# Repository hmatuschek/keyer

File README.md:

# Electronic touch CW keyer
This tiny circuit and its firmware implements a simple electronic CW keyer using capacitive touch-paddles. Hence it has absolutely no moving parts which eases the build of the mechanical part of the keyer a lot. 

The central logic of the keyer is implemented in software using a ATTiny 45 MCU. It implements a simple (mode A) electronic CW key. The capacitive touch interface is easy too. It basically measures the capacity of the metal paddles which changes as they get touched with the hand. In fact, the hardware measures the time needed to charge the paddles though a large resistor. This time increases significantly if the paddle is touched. 

The circuit provides a open-collector output to switch even simple transmitters which expect a straight key. Additionally an LED and a side-tone generator are present for practicing. The speed of the keyer can be set using a potentiometer in a range from 10WPM to 42WPM. Please note that the speed gets updated only while the key is idle.

## License
Both, the hard and software are licensed under the terms of the GNU Public License (GPL).

Copyright (C) 2015  Hannes Matuschek <hmatuschek at gmail dot com>

This program is free software; you can redistribute it and/or modify it under the terms of the GNU General Public License as published by the Free Software Foundation; either version 2 of the License, or (at your option) any later version.

This program is distributed in the hope that it will be useful, but WITHOUT ANY WARRANTY; without even the implied warranty of MERCHANTABILITY or FITNESS FOR A PARTICULAR PURPOSE.  See the GNU General Public License for more details.

You should have received a copy of the GNU General Public License along with this program; if not, write to the Free Software Foundation, Inc., 51 Franklin Street, Fifth Floor, Boston, MA 02110-1301 USA.

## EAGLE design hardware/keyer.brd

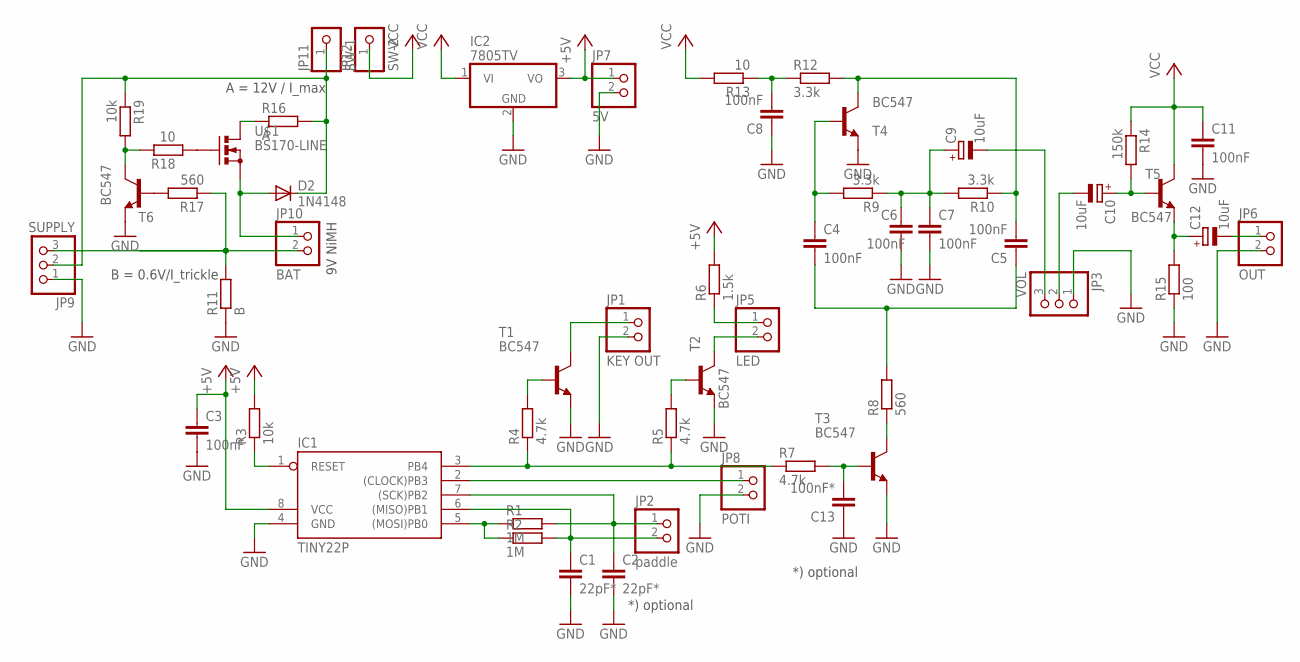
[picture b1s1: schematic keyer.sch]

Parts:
C1, C2: 22pF*; C050-025X075
C3: 100nF; C075-032X103
C4, C5, C6, C7, C8, C11: 100nF; C025-025X050
C9, C10, C12: 10uF; E2,5-6
C13: 100nF*; C025-025X050
D2: 1N4148; D-2.5
IC1: TINY22P; DIL08
IC2: 7805TV; TO220V
JP1: KEY OUT; 1X02
JP2: paddle; 1X02
JP3: VOL; 1X03
JP5: LED; 1X02
JP6: OUT; 1X02
JP7: 5V; 1X02
JP8: POTI; 1X02
JP9: SUPPLY; 1X03
JP10: BAT; 1X02
JP11: SW-1; 1X01
JP12: SW-2; 1X01
R1: 1M; 0204/5
R2: 1M; 0204V
R3: 10k; 0204/5
R4, R5, R7: 4.7k; 0204/5
R6: 1.5k; 0204/5
R8: 560; 0204V
R9, R12: 3.3k; 0204/5
R10: 3.3k; 0204/7
R11: B; 0204/5
R13: 10; 0204V
R14: 150k; 0204V
R15: 100; 0204/7
R16: A; 0204V
R17: 560; 0204/5
R18: 10; 0204/5
R19: 10k; 0204V
T1, T2, T3, T4, T5, T6: BC547; TO92-CBE
U$1: BS170-LINE; TO92-LINE

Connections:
+5V: C3.1, IC1.8 (VCC), IC2.3 (VO), JP7.1, R3.2, R6.2
GND: C1.2, C2.2, C3.2, C6.2, C7.2, C8.1, C11.2, C13.1, IC1.4 (GND), IC2.2 (GND), JP1.2, JP3.1, JP6.2, JP7.2, JP8.2, JP9.1, R11.1, R15.1, T1.E, T2.E, T3.E, T4.E, T6.E
unnamed: IC1.5 ((MOSI)PB0), R1.1, R2.1
unnamed: C2.1, IC1.7 ((SCK)PB2), JP2.1, R1.2
unnamed: C1.1, IC1.6 ((MISO)PB1), JP2.2, R2.2
unnamed: IC1.1 (RESET), R3.1
unnamed: IC1.2 ((CLOCK)PB3), JP8.1
unnamed: R4.2, T1.B
unnamed: JP1.1, T1.C
unnamed: IC1.3 (PB4), R4.1, R5.1, R7.1
unnamed: R8.1, T3.C
unnamed: R5.2, T2.B
unnamed: JP5.2, T2.C
unnamed: JP5.1, R6.1
unnamed: C4.1, R9.2, T4.B
unnamed: C13.2, R7.2, T3.B
unnamed: C5.2, R10.1, R12.2, T4.C
unnamed: JP9.3, JP10.2, R11.2, R17.1
unnamed: C6.1, C7.1, C9.+, R9.1, R10.2
unnamed: C4.2, C5.1, R8.2
unnamed: C8.2, R12.1, R13.1
unnamed: C9.-, JP3.3
unnamed: C10.-, JP3.2
unnamed: C10.+, R14.2, T5.B
unnamed: C12.+, R15.2, T5.E
unnamed: C12.-, JP6.1
unnamed: R17.2, T6.B
unnamed: D2.A, JP10.1, U$1.1 (S)
unnamed: R16.1, U$1.3 (D)
unnamed: R18.1, U$1.2 (G)
unnamed: R18.2, R19.2, T6.C
unnamed: D2.C, JP9.2, JP11.1, R16.2, R19.1
VCC: C11.1, IC2.1 (VI), JP12.1, R13.2, R14.1, T5.C

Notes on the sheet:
9V NiMH
A = 12V / I_max
B = 0.6V/I_trickle
*) optional

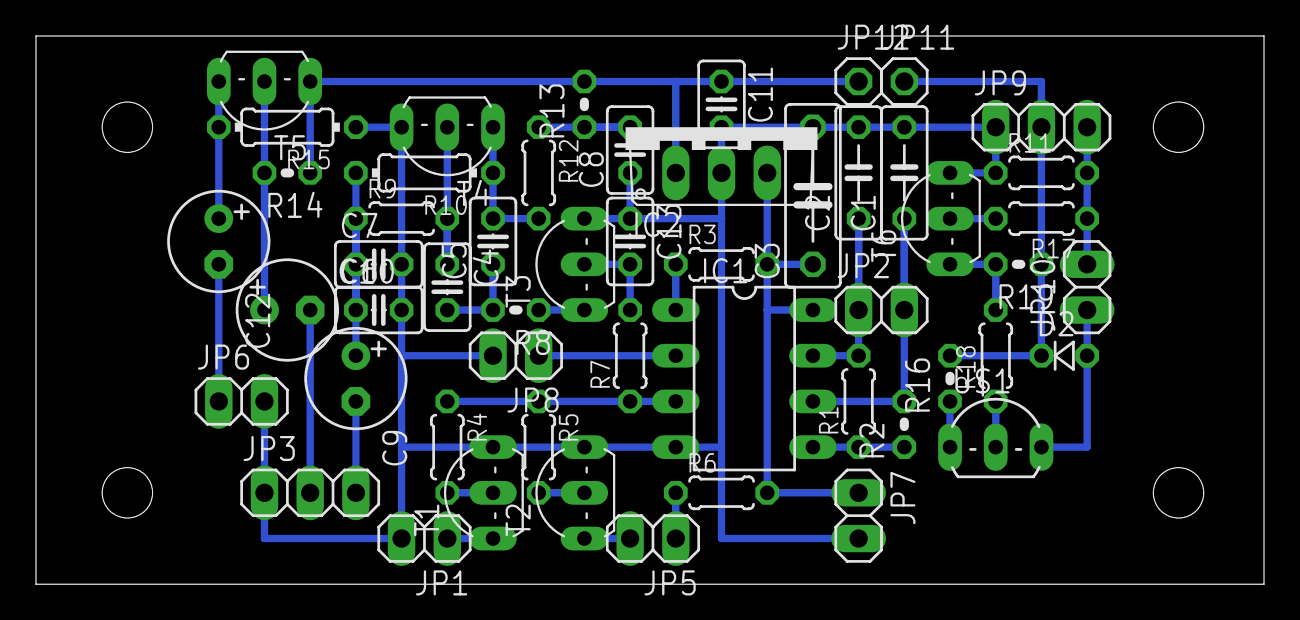
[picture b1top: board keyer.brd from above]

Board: 2 copper layers, 68.2 x 30.5 mm, 53 parts (0 on the bottom side), 33 nets.

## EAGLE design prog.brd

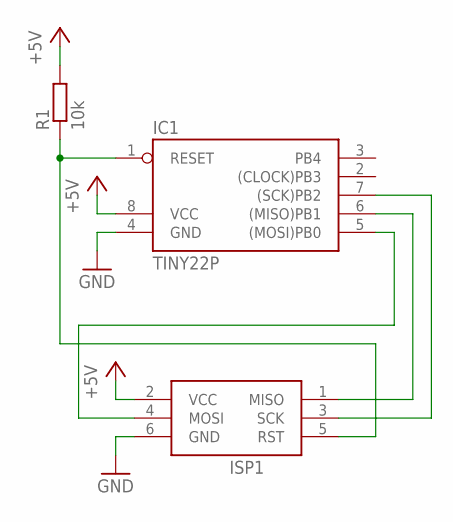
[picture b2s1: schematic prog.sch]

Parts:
IC1: TINY22P; DIL08
ISP1: AVRISP-6; AVRISP
R1: 10k; 0204/7

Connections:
+5V: IC1.8 (VCC), ISP1.2 (VCC), R1.2
GND: IC1.4 (GND), ISP1.6 (GND)
unnamed: IC1.1 (RESET), ISP1.5 (RST), R1.1
unnamed: IC1.5 ((MOSI)PB0), ISP1.4 (MOSI)
unnamed: IC1.6 ((MISO)PB1), ISP1.1 (MISO)
unnamed: IC1.7 ((SCK)PB2), ISP1.3 (SCK)

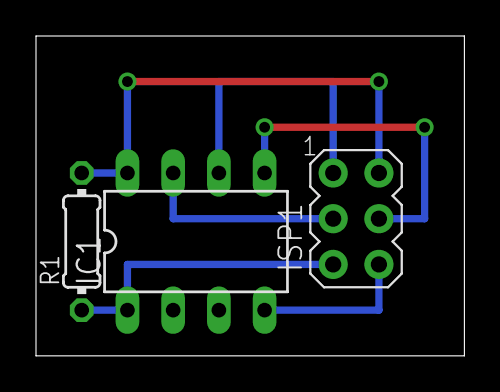
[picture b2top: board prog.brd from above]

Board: 2 copper layers, 23.8 x 17.8 mm, 3 parts (0 on the bottom side), 6 nets.

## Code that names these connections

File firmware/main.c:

/* Firmware for the CW touch key (paddle).
 *
 * (c) 2015, Hannes Matuschek <hmatuschek at gmail dot com>
 *
 * This firmware implements an electronic key using two simple metal paddles
 * (connected to PB1 & PB2) that are triggered by touching them. Touching a paddle causes the
 * capacity of the paddle to increase. This can be detected by measureing the time needed to charge
 * the paddle through a huge resistor (about 1MOhm). Touching the left paddle will generate a series
 * of dots (dit) while touching the right paddle will generate a series of dahses (dah). Touching
 * both paddles at the same time, a series of dot and dash alternations are generated. If the left
 * paddle was touched first, the series starts with a dash. If the right paddle was
 * touched first, the series starts with a dot. This is equivalent to the behavior of an
 * iambic CW key (mode A).
 *
 * The speed (between 10 and 43 WPM) can be chosen by a potentiometer connected to PB3 (ADC3). The
 * output is connected to PB4. This pin controls an open-collector output to controll the
 * transmitter, an LED and a 600Hz side-tone generator.
 */

#include <avr/io.h>
#include <avr/interrupt.h>
#include <util/delay.h>
#include <avr/cpufunc.h>
#include <avr/pgmspace.h>

/// Keep the delay short
#define MAX_DELAY (F_CPU/1000UL)
/// Helper macro to return the maximum of two values
#define max(a,b) (a<b ? b : a)


// LUT of 32 dit-lengths values (in ms),
// (approx) linear in WPM, from 10 to 42 WPM.
static const uint16_t dit_len_lut[] = {
  120, 109, 100,  92,  86,  80,  75,  70,
   67,  63,  60,  57,  54,  52,  50,  48,
   46,  44,  43,  41,  40,  39,  37,  36,
   35,  34,  33,  32,  31,  30,  29,  28};


/// Initializes the touch interface
void init_touch() {
  // set PB0 as output
  DDRB  |= (1 << DDB0);
  // set PB0 to 0
  PORTB &= ~(1 << DDB0);
  // set PB1 & PB2 as output (low Z, for now)
  DDRB  |= ((1 << DDB1) | (1 << DDB2));
  // set 0 (GND), keeps paddles discharged
  PORTB &= ~((1 << DDB1) | (1 << DDB2));
}

/// Read touch paddles, returns 0b00 if no paddle is touched,
/// 0b01 if only the left is touched, 0b10 if only the right is
/// touched and 0b11 if both are touched.
uint8_t read_touch(uint32_t thres) {
  // config sense pins as input (high impedance)
  DDRB  &= ~((1<<DDB1) | (1<<DDB2));
  // start charging, set PB0 -> 1
  PORTB |= (1<<DDB0);
  // delay
  for (uint32_t i=0; i<thres; i++) { _NOP(); }
  // check values (if the pin is still 0, the paddle is touched).
  uint8_t value = ((PINB>>1) & 0x03) ^ 0x03;
  // discharge paddles...
  PORTB &= ~(1<<DDB0);  // set PB0 -> 0
  // ... set sense pins as output (low impedance)
  DDRB  |= ((1<<DDB1) | (1<<DDB2));
  // ... set sense pin to 0 (GND)
  PORTB &= ~( (1<<DDB1) || (1<<DDB2) );
  // wait for a short time to discharge completely
  _delay_us(10);
  // done.
  return value;
}

/// Calibrate the touch interface
uint32_t calibrate_touch() {
  uint32_t thres = 1;
  // Increment threshold until touch detects no value
  while (read_touch(thres) && (thres<MAX_DELAY)) {
    thres++;
  }
  // Increase threshold for reliable detection
  // (this decreses the sensitivity for the sake
  // of reduced false-positives). The factor depends
  // on the hardware and may you need to experiment with
  // this value.
  return 2*thres;
}


/// Configures the timer interrupt to be triggered every 1ms.
void init_timer() {
  // Set Timer on Compare Match (CTC) mode
  TCCR0A = 0x02;
  // clock source CLK/16
  TCCR0B = 0x03;
  // -> 1ms
  OCR0A  = 125-1;
  // enable interrupt (OC 0A)
  TIMSK  = (1<<OCIE0A);
}


/// Configures the output.
void init_key() {
  // set PB4 as output
  DDRB  |= (1 << DDB4);
  PORTB &= ~(1 << DDB4);
}

/// Sets the output.
void key(uint8_t on) {
  if (on) { PORTB |= (1<<DDB4); }
  else { PORTB &= ~(1<<DDB4); }
}

/// Toggles the output.
void toggle_key() {
  PORTB ^= (1<<DDB4);
}


/// Initializes the ADC.
void init_adc() {
  // Set as input (high Z)
  DDRB  &= ~(1 << DDB3);
  // Disable digital input buffer of PB3
  DIDR0 |= (1 << ADC3D);
  // Config prescaler (no iterrupt, auto trigger, ADC still disabled)
  ADCSRA = (0 << ADEN) | (0 << ADSC) | (0 << ADATE) | (0 << ADIF) | (0 << ADIE) |
      (1<<ADPS2) | (1<<ADPS1) | (1<<ADPS0);
  // Vcc reference, ADC3 input
  ADMUX = (0<<REFS2) | (0<<REFS1) | (0<<REFS0) | (0<<ADLAR) |
      (0<<MUX3) | (0<<MUX2) | (1<<MUX1) | (1<<MUX0);
  // enable ADC
  ADCSRA |= (1<<ADEN);
}

/// Starts a new conversion.
void start_adc() {
  ADCSRA |= (1<<ADSC);
}

/// Returns true if the ADC is ready.
uint8_t adc_available() {
  return (0 == (ADCSRA & (1<<ADSC)));
}

/// Returns the ADC value as a 5-bit (0,...,31) value.
uint8_t adc_value() {
  return (ADCW>>5);
}

/// Returns the dit length in ms as defined by the ADC value.
uint16_t get_dit_len() {
  // Simply return the corresponding LUT value
  //return pgm_read_word_near(&dit_len_lut[adc_value() % 32]);
  return dit_len_lut[adc_value() % 32];
}


/** Possible states of the state machine. */
typedef enum {
  IDLE,         ///< Idle, wait for keys.
  SEND_DIT,     ///< Send a dit.
  SEND_DAH      ///< Send a dah.
} State;

/// The current state.
volatile State state = IDLE;
/// The last state.
volatile State last_state = IDLE;
/// The current dit length in ms.
/// Gets updated on startup.
volatile uint16_t dit_len = 60;
// Precomputed multiples of ditlen
volatile uint16_t dit_2len = 2*60;
volatile uint16_t dit_3len = 3*60;
volatile uint16_t dit_4len = 4*60;


int main(void)
{
  // Init timer interrupt
  init_timer();
  // Init touch interface
  init_touch();
  // Init output
  init_key();
  // Init ADC
  init_adc();

  // Calibrate the touch interface,
  // take the maximum threshold from 100 trials
  uint32_t thres = 0;
  for (uint8_t i=0; i<100; i++) {
    thres = max(thres, calibrate_touch());
  }

  // on calibration error
  // (delay threshold to large, sould not happen)
  while (MAX_DELAY == thres) {
    // -> blink trap
    toggle_key();
    _delay_ms(200);
  }

  // Measure speed setting...
  start_adc();
  // ... wait for the ADC to finish
  while (! adc_available()) { }
  // ... compute dit lenght
  dit_len = get_dit_len();
  // ... precompute some multiples of dit len
  dit_2len = 2*dit_len; dit_3len = 3*dit_len; dit_4len = 4*dit_len;

  // enable interrupts globally
  sei();

  // Go.
  state = IDLE;
  last_state = IDLE;

  // Poll paddles.
  while(1)
  {
    // If waiting for the next symbol...
    if (IDLE == state) {
      // ... dispatch by paddle state
      // (left -> dit, right -> dah, both -> alternate dit & dah)
      switch (read_touch(thres)) {
        // On left paddle
        case 0x01:
          last_state = IDLE;
          state = SEND_DIT;
          break;

        // On right paddle
        case 0x02:
          last_state = IDLE;
          state = SEND_DAH;
          break;

        // On both paddles alternate dit & dah
        case 0x03:
          if (SEND_DIT == last_state) {
            // If last state was a dit -> send dah
            last_state = SEND_DIT;
            state = SEND_DAH;
          } else {
            // If last state was a dah -> send dit
            last_state = state;
            state = SEND_DIT;
          }
          break;

        // Otherwise stay in idle
        default:
          break;
      }

      // If still in idle -> check speed dial and update dit length
      if ((IDLE == state) && adc_available()) {
        // If ADC is ready, update dit len
        dit_len = get_dit_len();
        // Precompute multiples of dit len
        dit_2len = 2*dit_len; dit_3len = 3*dit_len; dit_4len = 4*dit_len;
        // and restart measurement
        start_adc();
      }
    }
  }
}


ISR (TIMER0_COMPA_vect)
{
  static uint16_t count = 0;

  if (SEND_DIT == state) {
    // Send a dit (10, with additional pause)
    if (0 == count) {
      key(1); count++;
    } else if (dit_len == count) {
      key(0); count++;
    } else if (dit_2len == count) {
      last_state = SEND_DIT;
      state = IDLE;
      count = 0;
    } else {
      count++;
    }
  } else if (SEND_DAH == state) {
    // Send a dah (1110, with additional pause)
    if (0 == count) {
      key(1); count++;
    } else if (dit_3len == count) {
      key(0); count++;
    } else if (dit_4len == count) {
      last_state = SEND_DAH;
      state = IDLE;
      count = 0;
    } else {
      count++;
    }
  }
}

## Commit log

2015-12-21 Init.
2015-12-23 update...
2015-12-25 Cleanup.
2015-12-25 Added readme etc.
2015-12-25 Cleanup
2015-12-26 Fixed minor.
